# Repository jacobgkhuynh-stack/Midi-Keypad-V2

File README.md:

# Midi-Keypad-V2
Woah, it's the Midi Keypad (https://github.com/KaiPereira/MIDI-Keypad) but instead with 3 EC11 rotary encoders and 7 capacitive keys to reduce costs and make some sound!

So, I made this project for week 3 of Half Life by Hack Club and with it being the "DESIGN YOUR INSTRUMENT" week I followed the starter project guide "MIDI Keypad" and modified it to make it mine.

Here's the BoM
|Item                    |Qty|Supplier                  |Cost/item|Total Cost|link                                                                                                                                                                                                                                                                                                                                                                                                                                                                                                                                                                                                                                                       |
|------------------------|---|--------------------------|---------|----------|-----------------------------------------------------------------------------------------------------------------------------------------------------------------------------------------------------------------------------------------------------------------------------------------------------------------------------------------------------------------------------------------------------------------------------------------------------------------------------------------------------------------------------------------------------------------------------------------------------------------------------------------------------------|
|Waveshare ESP32-S3-Zero |1  |PiShare Store             |$7.41    |$7.41     |https://www.aliexpress.us/item/3256812546916539.html?spm=a2g0o.productlist.main.1.442d56e3U8lTk7&algo_pvid=33c486dc-489a-47be-a413-c6a68ad61944&algo_exp_id=33c486dc-489a-47be-a413-c6a68ad61944-0&pdp_ext_f=%7B%22order%22%3A%2264%22%2C%22eval%22%3A%221%22%2C%22fromPage%22%3A%22search%22%7D&pdp_npi=6%40dis%21USD%217.41%213.91%21%21%217.41%213.91%21%40210328df17929676871923703e0e24%2112000059219676552%21sea%21US%210%21ABX%211%210%21n_tag%3A-29910%3Bd%3A92917014%3Bm03_new_user%3A-29895%3BpisId%3A5000000218165390&curPageLogUid=Gcew5RvBwHOY&utparam-url=scene%3Asearch%7Cquery_from%3A%7Cx_object_id%3A1005012733231291%7C_p_origin_prod%3A|
|EC11 15mm 5 pcs         |1  |Components and parts Store|$3.47    |$3.47     |https://www.aliexpress.us/item/2251832761768596.html?spm=a2g0o.productlist.main.2.28891d23hrzXV8&algo_pvid=2c4b41eb-b321-4e54-8d23-4db71484b156&algo_exp_id=2c4b41eb-b321-4e54-8d23-4db71484b156-1&pdp_ext_f=%7B%22order%22%3A%2210%22%2C%22eval%22%3A%221%22%2C%22fromPage%22%3A%22search%22%7D&pdp_npi=6%40dis%21USD%213.47%211.09%21%21%213.47%211.09%21%402101c28d17929679569484202e0fd1%2166160447654%21sea%21US%210%21ABX%211%210%21n_tag%3A-29910%3Bd%3A92917014%3Bm03_new_user%3A-29895%3BpisId%3A5000000218165380&curPageLogUid=LN6pI8RJ4ROf&utparam-url=scene%3Asearch%7Cquery_from%3A%7Cx_object_id%3A32948083348%7C_p_origin_prod%3A           |
|PCB                     |1  |JLCPCB                    |$1.50    |$1.50     |https://jlcpcb.com/                                                                                                                                                                                                                                                                                                                                                                                                                                                                                                                                                                                                                                        |
|Estimated total shipping|1  |                          |         |$1.49     |                                                                                                                                                                                                                                                                                                                                                                                                                                                                                                                                                                                                                                                           |

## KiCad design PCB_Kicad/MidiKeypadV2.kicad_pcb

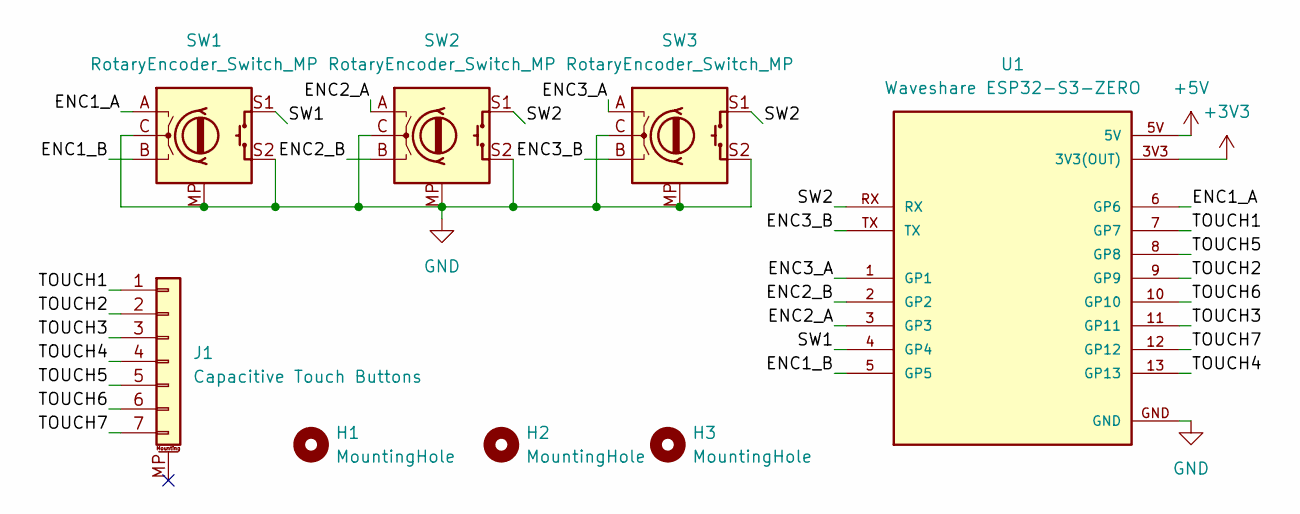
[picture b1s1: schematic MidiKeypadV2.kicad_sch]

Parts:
H1, H2, H3: MountingHole; MountingHole_2.7mm_M2.5
J1: Capacitive Touch Buttons; Capacitive Keys
SW1, SW2, SW3: RotaryEncoder_Switch_MP; RotaryEncoder_Alps_EC11E-Switch_Vertical_H20mm
U1: Waveshare ESP32-S3-ZERO; Waveshare ESP32-S3-Zero; PARTREV NA

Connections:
+3V3: U1.3V3 (3V3(OUT))
+5V: U1.5V
/ENC1_A: SW1.A, U1.6 (GP6)
/ENC1_B: SW1.B, U1.5 (GP5)
/ENC2_A: SW2.A, U1.3 (GP3)
/ENC2_B: SW2.B, U1.2 (GP2)
/ENC3_A: SW3.A, U1.1 (GP1)
/ENC3_B: SW3.B, U1.TX
/SW1: SW1.S1, U1.4 (GP4)
/SW2: SW2.S1, SW3.S1, U1.RX
/TOUCH1: J1.1, U1.7 (GP7)
/TOUCH2: J1.2, U1.9 (GP9)
/TOUCH3: J1.3, U1.11 (GP11)
/TOUCH4: J1.4, U1.13 (GP13)
/TOUCH5: J1.5, U1.8 (GP8)
/TOUCH6: J1.6, U1.10 (GP10)
/TOUCH7: J1.7, U1.12 (GP12)
GND: SW1.C, SW1.MP, SW1.S2, SW2.C, SW2.MP, SW2.S2, SW3.C, SW3.MP, SW3.S2, U1.GND

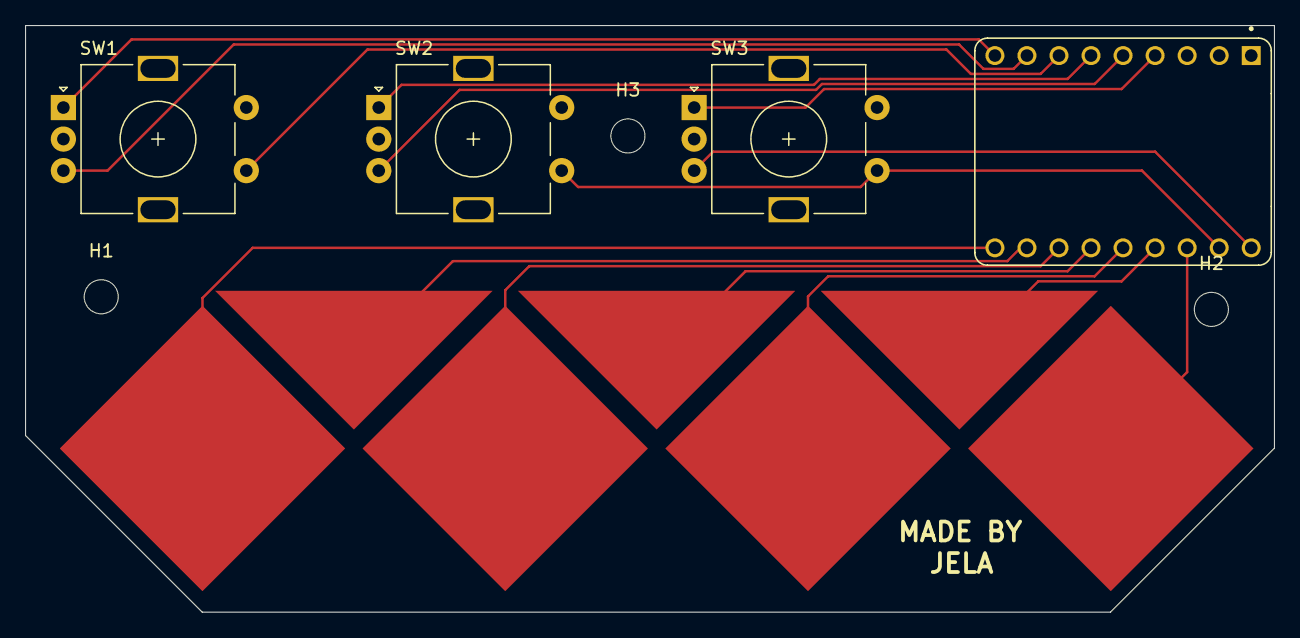
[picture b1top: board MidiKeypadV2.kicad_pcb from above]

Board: 2 copper layers, 99.0 x 46.5 mm, 8 parts (0 on the bottom side), 16 nets.
